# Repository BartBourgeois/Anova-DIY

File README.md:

# Anova Precision Cooker Pro: reverse engineering & firmware recovery

> **Public export.** This repository is a periodic export of a private working repo. Issues and pull
> requests are welcome, but changes are made upstream and arrive with the next sync. The unit's serial
> number and the support ticket number are withheld; see "Legal and safety" below.
> Last sync: 2026-11-14.

Reverse-engineering notes, tools and recovery work for the **Anova Precision Cooker Pro (AN600)**.
The first goal was to **get a unit that died after an interrupted OTA firmware update cooking again**, by fixing
its original main board if that could reasonably be done, otherwise by building our own. **Done on 6 November 2026,
on the original board.** The rest goes on: the hardware mapped further, the schematics, diagnostics software.

**Any%.** My update stopped at 75 %; yours may have frozen on another number, so this project goes by Any%.
Speedrunners know the category: finish, by whatever route works. We got there: nine days from the stalled update to
the first cook.

## It cooks again (6 November 2026)

Dead on 29 October, the morning after an update stalled at 75 %. Cooking again on 6 November, on its original main
board: the buttons and the display, Wi-Fi and the app, and a 54 °C test cook held on point for ten minutes.

- **What was wrong:** the Wi-Fi chip had locked itself. Its security-alert counter stood at the limit, where the
  chip refuses to run until it is reprogrammed. The update's leftovers on the flash were harmless (the chip's own
  safeguard undoes them), the update never reached the Bluetooth chip, and the power board was fine all along.
  What raised the alerts is still open.
- **How it was fixed:** both chips' flash backed up first, each read twice with the same checksum. Then the Wi-Fi
  chip was reprogrammed through its own boot loader with the chip maker's tool: the current firmware, and the unit's
  own files carried over from the backup. Only the chip maker's documented procedures; no firmware is published here.
- **The story:** [Day six: it cooks again](blog/posts/2026-11-06-it-cooks-again.md). The record:
  [timeline](docs/timeline.md). The procedures: the [flash backup handbook](docs/flashbackup/index.md) and the
  [recovery handbook](docs/recovery/index.md).

> Not affiliated with or endorsed by Anova Applied Electronics, Inc. (Anova Culinary). Everything here is at your own risk.
> The power board carries **mains voltage**. Never open or probe a unit that is plugged in.

## Why

*Written on 2 to 4 November, while the cooker was dead, and left as it was written. Its questions are answered in
[It cooks again](#it-cooks-again-6-november-2026).*

I paid what a premium product from a premium brand costs, about $450, and expected exactly that. The cooker died
right after a firmware update was interrupted. Not dropped, not flooded, not abused: the update stalled at 75 %, and
after a power cycle the unit was dead. No beep, no display, nothing. I have no doubt the update killed it: it was the only event, the timing matches, nothing else happened.
By this repo's own standard that stays "likely" until a measurement rules out a coincidental power-supply failure.
The first one, on 4 November, points that way: the power board still puts 5.01 V on the connector with the main board
unplugged. Whether it holds up under load is the next check.

In my view that should not be possible in 2026. A $10 smart plug routinely survives a botched update: it keeps the
old firmware until the new one has proven itself. The Wi-Fi chip in this cooker even has that mechanism built in
(TI documents an OTA rollback for it). Yet here we are.

I'll own my part. The cooker worked perfectly, and I updated it anyway. I work in IT, where update discipline is
drilled into you, and I also know the older rule: if it isn't broken, don't fix it. So yes, I pressed the button.
But in my book, a vendor that offers updates is responsible for what an interrupted one does. The hardware that
lets a device survive a botched update is a second copy of the firmware in flash, a dollar's worth of memory at
most. This cooker has 8 MiB of flash, and its chip's maker documents a rollback mechanism for exactly this case
([recovery-strategy.md](docs/firmware/recovery-strategy.md)). It didn't save my cooker. Finding out why is part of
this project.

And that is the most interesting question in this whole story. The mechanism exists on this very board, so there are
only three ways to end up here: the firmware doesn't use it; or the update touched something it doesn't cover (the
BLE chip, the file system itself); or the failure isn't in the Wi-Fi chip at all. The flash dump will tell. Whichever
answer it is, it goes here, with the evidence.

Anova's answers so far (ticket opened 2026-10-29): leave it plugged in overnight; then that the unit is out of
warranty; then 10 % off a new one. For perspective: 10 % is the usual newsletter sign-up discount on Anova's own
site, and the Pro itself has sold at about half price in seasonal promotions (Amazon US, Black Friday 2020;
[sources](docs/references.md#anova)). On 2026-11-01 I asked for one of four things: a firmware image with recovery
instructions, a replacement main board at my cost, a mail-in reflash, or a refurbished unit. None of the four came:
the reply (2026-11-02) was a reset procedure on the touch panel, which had been dark since the update. On 2026-11-06,
with the cooker cooking again, I told them how it was fixed and offered the details to their firmware team; on
2026-11-08 they forwarded my account to their engineering and development teams. The whole exchange is on record, word for word: [correspondence](docs/correspondence.md). To me, a discount on
a replacement isn't support, it's a sales offer.

It's sad, and I feel tricked: a premium price should buy an update process that can't kill the device. I'd rather
spend thousands of euros on debugging hardware, beta boards and DIY electronics than buy a new Anova. Spent on
tools so far: about €545, two days in ([list](docs/hardware/bench-setup.md#spent-so-far-2026-11-02)).

So I'll keep at this until this dead Pro cooks again, whatever it takes. If Anova helps: good, cheaper for me, and I'll
say so here. If not, make no mistake, the cooker will cook. Everything I learn on the way is in this repo, so the next
person with a dead one doesn't start from zero.

This repository stays online, whatever the outcome. I will not delete it. It documents the progress and the process as
they happen: every change upstream is published within seconds. The public repository is a snapshot by design, the
current state and nothing else; the dated record is the [timeline](docs/timeline.md), and when a statement of
substance about the cooker turns out wrong, the correction goes there with its date. It is what it is.

raptox

## What this project wants

1. **This cooker cooking again.** **Done, 6 November 2026**, on its original main board
   ([how](#it-cooks-again-6-november-2026)). Nothing waited on anyone.
2. **A documented recovery path for every Precision Cooker Pro that fails the same way.** Everything learned here is
   public under an open licence ([LICENSE.md](LICENSE.md)), so the next owner starts from this page, not from zero.
3. **From Anova, any of the four things asked on 2026-11-01:** a firmware image with recovery instructions, a
   replacement main board at my cost, a mail-in reflash, or a refurbished unit. Or, better for every owner: an
   official, documented recovery procedure for units out of warranty. Help gets credited here, in full.

How the work is done: read-only first, a verified backup before any write, every claim with a confidence label and
a source, every step in the [timeline](docs/timeline.md). This project documents a repair. It distributes no firmware
and publishes no way around any protection (see [Legal and safety](#legal-and-safety)).

## The patient

| | |
|---|---|
| Model | Anova Precision Cooker Pro, type **AN600-20** (EU, 220-240 V) |
| FCC ID | [`2APBOAN600`](https://fccid.io/2APBOAN600) (granted 2018-09-16, tested as AN600-10 / 120 V) |
| Symptom | OTA update via the Anova app stalled at 75%. After a power cycle the unit is completely dead: no beep, no display, no LEDs, and nothing on Bluetooth or Wi-Fi. |
| Status | **Cooking again since 2026-11-06**: the Wi-Fi chip had locked itself; reprogrammed ([how](#it-cooks-again-6-november-2026)). |
| Reference | A second, **working** Precision Cooker Pro is available for read-only comparison. |

Full story: [docs/incident.md](docs/incident.md). Everything since then, dated: [docs/timeline.md](docs/timeline.md).
The narrative, in instalments: [blog](blog/index.md).

**Website:** <https://cooked.raptox.be/>, rebuilt from this repo on every push.

## What's inside

From raptox's unit (main board, 2026-11-01) and the FCC photos (everything else).

| Board | Key parts |
|---|---|
| **Main board** `ANOVA_PRO_MAIN_V2.0` | **U1 TI CC3220S** Wi-Fi MCU, boots from **U15/U16 XMC XM25QH64A** (8 MiB SPI NOR, SOP-8 208 mil) · **U7 TI CC2640R2F** BLE MCU (internal flash) · unidentified U14 `T3018` (QFN-40), U13 `4637` (QFN-20, next to the speaker) · debug: J29 (1x3, empty: the serial link between the two chips, both directions, and the Wi-Fi chip's boot-loader port), J14 (4-way DIP footprint, empty, the Wi-Fi chip's three boot straps), Tag-Connect J37/J38, TP groups · 30-pin FPC J8 to the power board · J9 speaker · 6 touch keys, about 135 discrete LEDs forming 3 x 4 seven-segment digits |
| **Power board** `ANOVA_PRO_POWER_REV01` | AC/DC flyback daughterboard (F1 T2A/250V) · heater relay · main fuse · DC/DC buck (6.8 uH) · several unidentified ICs · 30-pin FPC J8 · wire terminals for heater/pump/sensors · PCB "finger" that probably carries the water-temperature sensor |

Details: [docs/hardware/overview.md](docs/hardware/overview.md) ·
[main board](docs/hardware/main-board.md) · [power board](docs/hardware/power-board.md) ·
[component list](docs/hardware/components.md) · [opening the head](docs/hardware/disassembly.md) ·
[bench setup & debugging](docs/hardware/bench-setup.md) · [photo log](docs/photos.md)

## Annotated photos

**raptox's unit**, main board component side, stitched from 335 microscope frames (2026-11-03):

At 100 % (229 px/mm): the zoomable [mosaic viewer](docs/mosaics.md) or the
[lossless PNG](https://github.com/BartBourgeois/Anova-DIY/releases/download/mosaics/2026-11-03_main_component-side_mosaic.png).

The first phone photo of the same side (2026-11-01): [annotated](images/annotated/main_component-side_own.png).

**All photos in this project are our own unless marked otherwise.** The images below marked "FCC" come from the
public FCC filing for this product (FCC ID 2APBOAN600, internal-photos exhibit 3999178, 2018 sample) and carry that
source in their legend.

FCC sample (2018), source: FCC ID 2APBOAN600, exhibit 3999178:

| | |
|---|---|
|  |  |
| Main board, component side | Main board, LED / touch side |
|  |  |
| Power board, top | Power board, bottom |
|  |  |
| Head opened (assembly) | Front bezel (from the back) |

Box colour = category, outline = confidence (solid confirmed, dashed likely, dotted guess).
Click an image for its callout table.

## Roadmap

Two cases, both planned, in [docs/roadmap.md](docs/roadmap.md): Anova helps (unlikely; documented in full if it
happens, and the repair part ends there), or we do it ourselves, all the way, with every step the tools allow. Either
way the project doesn't stop at the point of no return, which has passed.

The headline steps of the do-it-ourselves case: **4K microscope imaging of every board**, tile by tile, into
measurable mosaics; transillumination for the inner copper layers; **reverse-engineering the schematics**, net by net,
since Anova's are confidential in the FCC filing; logic analyser and UART on the boot sequence; a verified dump of the
flash; rehearsals of every write on a known-good chip; and, if the board can't be fixed, a board of our own. The
phase view below is the short version.

| Phase | Goal | Status |
|---|---|---|
| 0 | Document hardware from the public FCC filing | **done (first pass)** |
| 1 | Open the dead unit: own high-res photos, read chip markings, measure supply rails; compare (read-only) with the working unit | **in progress**: opened, main board photographed, markings read; main board's component side stitched from microscope frames at about 229 px/mm ([photo log](docs/photos.md#2026-11-03-microscope-mosaic-main-board-component-side)); next: the other sides and backlight; the power board's 5 V measured (4 Nov), the rails under power todo |
| 2 | Find and map debug interfaces: J29, J37/J38 (Tag-Connect), DIP J14, test points; CC3220 SOP straps, UART, JTAG/SWD; CC2640R2F cJTAG. Identify power-board U2 (MCU?) and map the J8 pinout unpowered. Draw the schematics from the images and the continuity map. | **in progress**: J8's supply and ground (4 Nov); the flash bus, the three boot straps with their pull-downs, the serial header J29 and nine bare pads measured to the chips (5 Nov, [test points](docs/hardware/testpoints.md)); J37 and J8's signal lines next |
| 3 | **Back up first**: full read-only dump of the CC3220 serial flash (and of the CC2640R2F flash if readable), read twice and hash-verified | **done**, 6 Nov: the serial flash by clip with the Wi-Fi chip held in reset, the CC2640R2F over its cJTAG port; each read twice, identical, copied off the machine ([flash backup handbook](docs/flashbackup/index.md)) |
| 4 | Analyse the dumps: SimpleLink filesystem layout, OTA state, which chip the failed update targeted | **done**, 6 Nov: the file system intact, the interrupted update in a state the chip rolls back; the CC2640R2F untouched by it; the CC3220 **locked** (its security-alert counter at the limit) ([timeline](docs/timeline.md)) |
| 5 | Recovery, depending on Phase 4. The broken file alone, replaced through the UARTLOAD boot loader, keeps the unit's network address and cloud identity, but a production-mode boot loader refuses file writes (rehearsed 6 Nov); then a full image with the unit's own readable files carried over from the backup, or RET_FACTORY_IMAGE (both erase the protected ones); a CC2640R2F reflash if that chip is the victim | **done**, 6 Nov: a full image through the UARTLOAD boot loader, the current firmware with the unit's own files from the backup; the lock cleared, **the cooker cooks** ([the story](blog/posts/2026-11-06-it-cooks-again.md)) |
| 6 | Diagnostics software (UART console, flash-dump parser, BLE/Wi-Fi local API client, ...) | later |
| B | If the board can't reasonably be fixed: our own main board (ESP32-S3, headless first), or our own firmware on the original CC3220 | **committed fallback** ([plan B](docs/plan-b-custom-mainboard.md)) |

The recovery reasoning lives in [docs/firmware/recovery-strategy.md](docs/firmware/recovery-strategy.md).

Phases 1-2 are run as an **open exploration**: no gates, every tool used to learn as much as it can, route chosen
only when the findings make it obvious.

## Legal and safety

- **Not affiliated.** Anova and Precision Cooker are trademarks of Anova Applied Electronics, Inc., used here only
  to identify the product. This project is not affiliated with, endorsed by or sponsored by Anova.
- **Own device, for repair.** Everything here comes from examining a device raptox owns, from public FCC filings and
  from public chip-maker documentation (TI). The aim is to repair it. The procedures described are the ones TI
  documents for its own chips; in the author's reading (not legal advice), nothing here circumvents a technical
  protection.
- **Never distributed:** Anova firmware, flash dumps or fragments of them; keys, certificates or credentials; anything
  that gives access to Anova's servers; Anova's user manual; the FCC exhibit PDFs themselves (public at
  [fccid.io/2APBOAN600](https://fccid.io/2APBOAN600), SHA-256 in [docs/references.md](docs/references.md)).
- **Statements about Anova** are dated facts from the support correspondence, quoted word for word on the
  [correspondence page](docs/correspondence.md) or paraphrased, or opinions labelled as such. Anova staff are never named.
- **Safety, no warranty.** The power board carries mains voltage, which can kill. Opening the unit voids its warranty
  and its CE/FCC certification, radio included; a modified unit is not a certified appliance. Never leave a modified
  heater unattended. Everything here is at your own risk, without warranty or liability of any kind
  ([LICENSE.md](LICENSE.md), at the root of the public repo).
- The author is an engineer, not a lawyer. This is engineering documentation, not legal advice.
- The full statement of the bounds this project works within, for the United States, for Belgium and the EU, and for
  everywhere else: [docs/legal.md](docs/legal.md).

## Sources

Hardware information comes from raptox's own unit and the public FCC filing for `2APBOAN600` (the schematics and block
diagram are confidential and not available). See [docs/references.md](docs/references.md).

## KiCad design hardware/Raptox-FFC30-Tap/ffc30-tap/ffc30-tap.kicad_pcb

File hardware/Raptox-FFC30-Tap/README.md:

# FFC30 tap

A pass-through board for a 30-way flat flex cable (FFC) at 0.5 mm pitch. It sits between two boards, passes every
line straight through, and brings each line out on a 2.54 mm pin with a ground pin beside it, for a logic analyser
such as the DSLogic Plus. It was made for the Anova Precision Cooker Pro's J8 link (main board to power board,
[pinout](../../docs/hardware/j8.md)), but nothing on the board is specific to that cooker.

**Status (2026-11-12): rev C ordered at JLCPCB** (order number and date to add). The order files are in [ffc30-tap/fab/](ffc30-tap/fab/); see
[Ordering at JLCPCB](#ordering-at-jlcpcb).

## Rev C
- 80 x 70 mm (JLCPCB's assembly asks for at least 70 x 70 mm), 4 layers, 1.6 mm, black solder mask.
- Two sockets, the same part on both sides: HanElectricity **05A20L30P** (LCSC C5362159), bottom contact, flip lock,
  2.0 mm high, for 0.3 mm FFC. Contacts on one face only, so neither cable can go in upside down (rev A's sockets
  allowed it). Land pattern from HanElectricity's drawing 05A20LXX (rev A, 2015-05-03): signal pads 0.30 x 1.25 mm,
  mounting pads 2.00 x 3.00 mm. The body's front (cable entry) is flush with the board edge (`likely`, within about
  0.2 mm: the drawing gives the depth, the pin tips' place on the pads is estimated).
  The first pick, XKB X05A20L30T (C2880811), was out of stock at JLCPCB; its land pattern is almost the same.
- Two 2x15 headers (LCSC C56496, 2.54 mm, straight). Block 1 = lines 1-15, block 2 = lines 16-30, each line with a
  ground pin beside it. Pin 1 at the bottom of block 1, pin 16 at the bottom of block 2.
- Lines 1-15 run on the top layer, lines 16-30 on the bottom layer (through a via column next to each socket).
  In1 and In2 are solid ground planes that join both ground columns.
- Silkscreen: pin numbers, the ground boxes, the title and cooked.raptox.be. Everything else is in this file.

## Using it
1. **Cables:** both of the same type (contacts on the same side at both ends, "type A"), contacts down into the
   sockets.
2. **The board whose pin numbers you want goes in the LEFT socket.** Header pin n is then its pin n, if its
   connector has bottom contacts and numbers its pins like these sockets (pin 1 on the left, seen from where the
   cable enters). Otherwise header pin n is its pin 31 - n. The lines pass through correctly either way.
   - Anova: the main board's cable (J8) in the left socket, the power board's in the right. Header n = J8 pin n
     (`likely`: J8 has bottom contacts by the cable photos, and its pin 1 position is from the microscope mosaic).
3. **Before power,** with only the left board's cable in, ring a pin you know to the header.
   Anova: header pins 1-6 ring together (the 5 V supply), and so do 10, 11, 17, 19, 22, 23 and 30 (ground).
4. **Ground:** the ground columns float until a jumper cap joins a line that *is* ground to the ground pin beside
   it. One or two caps are enough for slow signals (DreamSourceLab's DSView guide: one common ground below about
   5 MHz). A cap on a supply line shorts the supply. Anova: caps only on 10, 11, 17, 19, 22, 23 or 30, never on 1-6.
5. **Probes:** the signal lead on a line pin, its ground lead on the ground pin beside it.
6. **Mains:** a PC-grounded analyser connects the PC's earth to the board's ground. With a mains-powered board in
   the chain, check that its ground is isolated from mains first (for the cooker:
   [bench setup](../../docs/hardware/bench-setup.md)).
7. **Underneath:** the header pins stick out about 1.4 mm under the board (3 mm tails through 1.6 mm), plus solder.
   Stand the board on four M2 nylon standoffs, at least 6 mm, in the corner holes, or on a non-conductive surface.
   Never on metal (a bench, a tool, the cooker's housing): it joins pins, and a supply line on ground shorts the
   supply.

## Ordering at JLCPCB
Three files, all in `ffc30-tap/fab/`:

| Step | File | Settings |
|---|---|---|
| PCB | `ffc30-tap_gerbers_JLC.zip` | 4 layers, 80 x 70 mm (read from the files), 1.6 mm, **black** solder mask, the default 4-layer stackup |
| Assembly | | **Standard** PCBA (the headers are wave soldered, which Economic doesn't do), top side, edge rails added by JLCPCB (on the 80 mm sides; the sockets are on the 70 mm sides), **Confirm Parts Placement: Yes** |
| BOM | `jlc_bom.csv` | J1, J2 = C5362159 (socket); J3, J4 = C56496 (2x15 header). Both are extended parts; check stock |
| Placement | `jlc_cpl.csv` | Check every part in the placement preview, then confirm |

The CPL already carries two corrections for JLCPCB's own part models (measured in their placement viewer on
2026-11-12, set in `build_fab.py`; the copper itself follows the makers' drawings):
- **Sockets J1, J2:** JLCPCB's model of C5362159 sat 2.0 mm toward the board edge from the pads, so the CPL moves each
  socket 2.0 mm toward its pads. With that, the model's pins end about 0.15 mm inside the pads' tips and its body
  starts about 0.8 mm from them, as the footprint assumes.
- **Headers J3, J4:** JLCPCB's model of C56496 lies across the board at 0 degrees; the CPL turns them 90 degrees.

Still check in the placement preview, against [the render](ffc30-tap/render_top.png): the sockets' cable openings
face the board edges and their pins sit on the 30 pads; the headers stand over their two columns.

First quote (2026-11-12, 5 boards, before shipping): PCB EUR 14.40 (black mask EUR 7.20 of it), Standard PCBA
EUR 43.39, total EUR 57.79; PCB 3 days, assembly 5-6 days.

## Regenerating
The board is generated from code: change `generate_board.py`, never the `.kicad_pcb` by hand. With KiCad 10's own
Python, in `ffc30-tap/`:

```sh
"<KiCad 10>/bin/python.exe" -I generate_board.py   # board, footprint library, fp-lib-table
"<KiCad 10>/bin/python.exe" -I build_fab.py        # DRC (must be clean), gerbers, drill, BOM, CPL, renders
```

## Revisions
- **rev A** (2026-11-12, [revA/](revA/), not ordered): 2 layers, one 2x15 header, sockets with contacts on both faces
  (X05A20H30G). One cable inserted upside down mirrors the bus (pin n to 31 - n): on the cooker that feeds the main
  board backwards. Its header numbers read reversed with the main board in the socket marked HOST.
- **rev B** (drawn, not kept): four columns of 15 (ground, line, line, ground) with ground planes.
- **rev C** (2026-11-12): this board. Its first build still carried rev A's socket pads; the X05A20LXXT land pattern
  replaced them the same day, before any order (the board grew to 80 x 70 mm). The same day the socket became
  HanElectricity's 05A20L30P (XKB's was out of stock at JLCPCB), with its own land pattern.

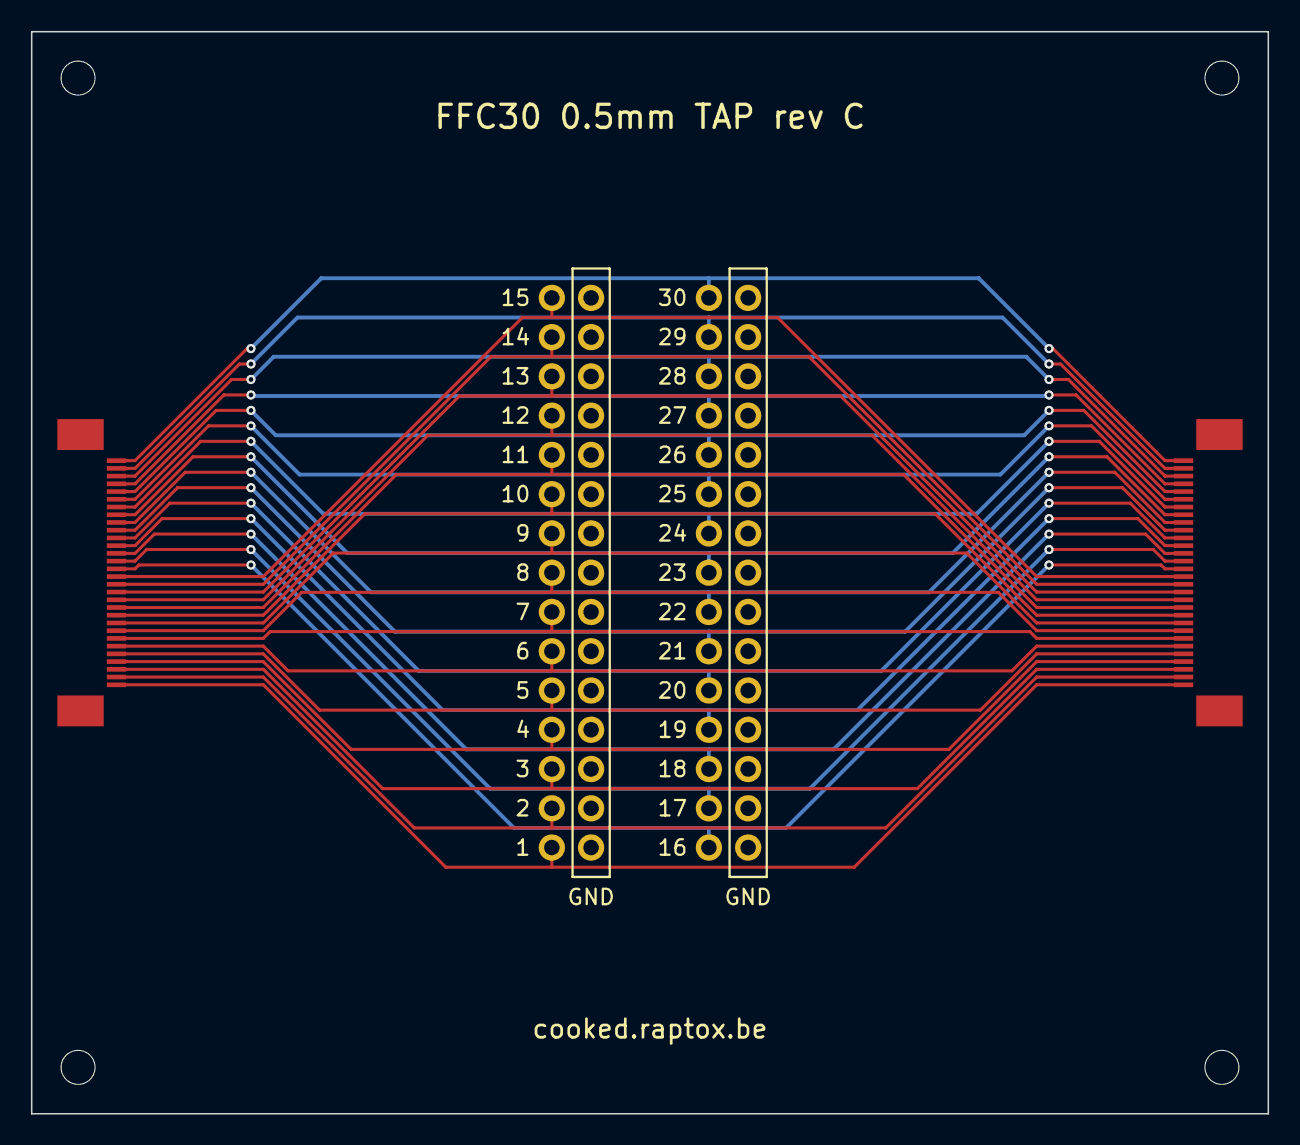
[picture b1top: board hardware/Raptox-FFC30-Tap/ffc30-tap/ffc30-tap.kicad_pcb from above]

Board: 4 copper layers, 80.0 x 70.0 mm, 8 parts (0 on the bottom side), 31 nets.

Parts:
H1, H2, H3, H4: M2; MountingHole_2.2mm_M2
J1, J2: HanElectricity 05A20L30P; HanElectricity_05A20L30P_FPC30_P0.5mm
J3, J4: BOOMELE 2.54-2*15P (2x15 2.54 mm male, straight); PinHeader_2x15_P2.54mm_Vertical_centred

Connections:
GND: J3.2, J3.4, J3.6, J3.8, J3.10, J3.12, J3.14, J3.16, J3.18, J3.20, J3.22, J3.24, J3.26, J3.28, J3.30, J4.2, J4.4, J4.6, J4.8, J4.10, J4.12, J4.14, J4.16, J4.18, J4.20, J4.22, J4.24, J4.26, J4.28, J4.30
P01: J1.30, J2.1, J3.29
P02: J1.29, J2.2, J3.27
P03: J1.28, J2.3, J3.25
P04: J1.27, J2.4, J3.23
P05: J1.26, J2.5, J3.21
P06: J1.25, J2.6, J3.19
P07: J1.24, J2.7, J3.17
P08: J1.23, J2.8, J3.15
P09: J1.22, J2.9, J3.13
P10: J1.21, J2.10, J3.11
P11: J1.20, J2.11, J3.9
P12: J1.19, J2.12, J3.7
P13: J1.18, J2.13, J3.5
P14: J1.17, J2.14, J3.3
P15: J1.16, J2.15, J3.1
P16: J1.15, J2.16, J4.29
P17: J1.14, J2.17, J4.27
P18: J1.13, J2.18, J4.25
P19: J1.12, J2.19, J4.23
P20: J1.11, J2.20, J4.21
P21: J1.10, J2.21, J4.19
P22: J1.9, J2.22, J4.17
P23: J1.8, J2.23, J4.15
P24: J1.7, J2.24, J4.13
P25: J1.6, J2.25, J4.11
P26: J1.5, J2.26, J4.9
P27: J1.4, J2.27, J4.7
P28: J1.3, J2.28, J4.5
P29: J1.2, J2.29, J4.3
P30: J1.1, J2.30, J4.1

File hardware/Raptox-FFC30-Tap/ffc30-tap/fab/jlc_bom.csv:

Comment,Designator,Footprint,LCSC Part #
HanElectricity 05A20L30P FPC 30P 0.5mm bottom contact flip,"J1,J2",FPC-30P-0.5mm,C5362159
2x15 pin header 2.54mm straight male (6 mm pins),"J3,J4",PinHeader_2x15_P2.54mm,C56496

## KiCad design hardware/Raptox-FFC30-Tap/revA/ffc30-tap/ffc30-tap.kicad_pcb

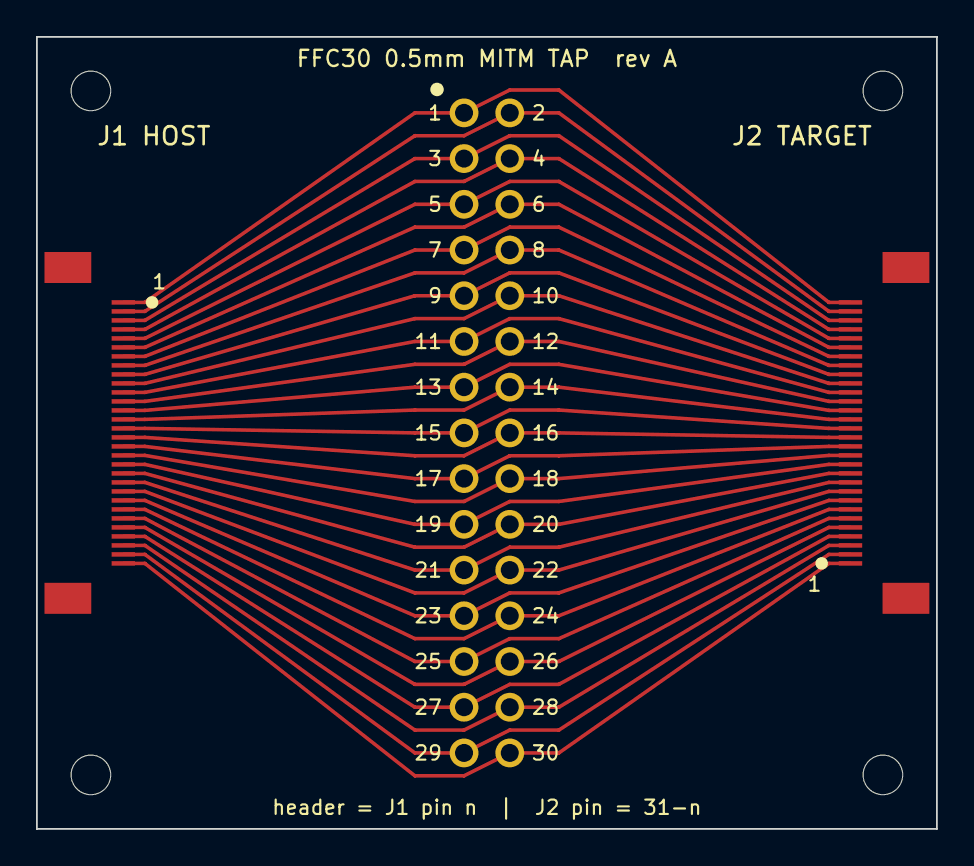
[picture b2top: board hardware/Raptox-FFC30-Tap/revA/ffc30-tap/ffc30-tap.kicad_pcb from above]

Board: 2 copper layers, 50.0 x 44.0 mm, 7 parts (0 on the bottom side), 30 nets.

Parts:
H1, H2, H3, H4: M2
J1: FPC30 host side; XKB_X05A20H30G_FPC30_P0.5mm
J2: FPC30 target side; XKB_X05A20H30G_FPC30_P0.5mm
J3: Tap 2x15 2.54mm; PinHeader_2x15_P2.54mm_tap

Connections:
S01: J1.1, J2.30, J3.1
S02: J1.2, J2.29, J3.2
S03: J1.3, J2.28, J3.3
S04: J1.4, J2.27, J3.4
S05: J1.5, J2.26, J3.5
S06: J1.6, J2.25, J3.6
S07: J1.7, J2.24, J3.7
S08: J1.8, J2.23, J3.8
S09: J1.9, J2.22, J3.9
S10: J1.10, J2.21, J3.10
S11: J1.11, J2.20, J3.11
S12: J1.12, J2.19, J3.12
S13: J1.13, J2.18, J3.13
S14: J1.14, J2.17, J3.14
S15: J1.15, J2.16, J3.15
S16: J1.16, J2.15, J3.16
S17: J1.17, J2.14, J3.17
S18: J1.18, J2.13, J3.18
S19: J1.19, J2.12, J3.19
S20: J1.20, J2.11, J3.20
S21: J1.21, J2.10, J3.21
S22: J1.22, J2.9, J3.22
S23: J1.23, J2.8, J3.23
S24: J1.24, J2.7, J3.24
S25: J1.25, J2.6, J3.25
S26: J1.26, J2.5, J3.26
S27: J1.27, J2.4, J3.27
S28: J1.28, J2.3, J3.28
S29: J1.29, J2.2, J3.29
S30: J1.30, J2.1, J3.30
